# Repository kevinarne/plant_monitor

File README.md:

# Purpose
As I seek to both improve the lives of my plants and learn more about Python development, I've decided to start instrumenting my plants with some sensors like light and weight sensors.

# Current State
There are three kinds of sensors currently supported: CdS light sensor hooked up to an Arduino (directly connected to Pi via serial), CdS light sensor hooked up to an ESP32 (wireless), and load cell hooked up to an ESP32 (wireless). Each of these connects to a Raspberry Pi-hosted MySQL database on my local network.

The wireless sensors add data to the database via an HTTP request handled by a PHP script on the local server. The wired sensor is polled via serial regularly by a python script scheduled with crontab.

# Current Event Types
* 10-bit CdS light sensor (wired Arduino Nano)
* 12-bit CdS light sensor (wireless ESP32)
* Manual weighing
* Load cell weighing (wireless ESP32)
* Wiring (for shaping trees)
* Removed wire
* Root pruning
* Plant status (out of 5 stars)

# Potential Next Steps
* Visualize the collected light sensor data
* Create more ESP32-powered sensors
* Migrate from serial light sensor to ESP32 light sensor
* Add a user id column to the plant_events, sensors, and plants tables
* Convert to Flask
* Add web page to store wireless connections to ESP32 sketches
* Store tare value in EEPROM on ESP32

# Flask Conversion Next Steps
* Create routes.py
* Migrate database to an sqlite database
* Create user database
* Create web interface for adding weight
* Create plant status page
* 

# Current Tables
* plant_events - Tracks values recorded by various sensors, their associated plants, and things like watering, repotting, pruning, weighing, and even light. Currently it only tracks light.
* plants - Dictionary relating ids used in plant_events and actual plants.
* event_codes - Dictionary correlating events with unique ids.
* sensors - Details of the sensors.

# Set Up
Python 3 Libraries:
* datetime
* itertools
* python-decouple
* pyserial
* pymysql
* matplotlib
* numpy
* smtplib

See /setup/README.md for more details on setting up this project, including database setup.

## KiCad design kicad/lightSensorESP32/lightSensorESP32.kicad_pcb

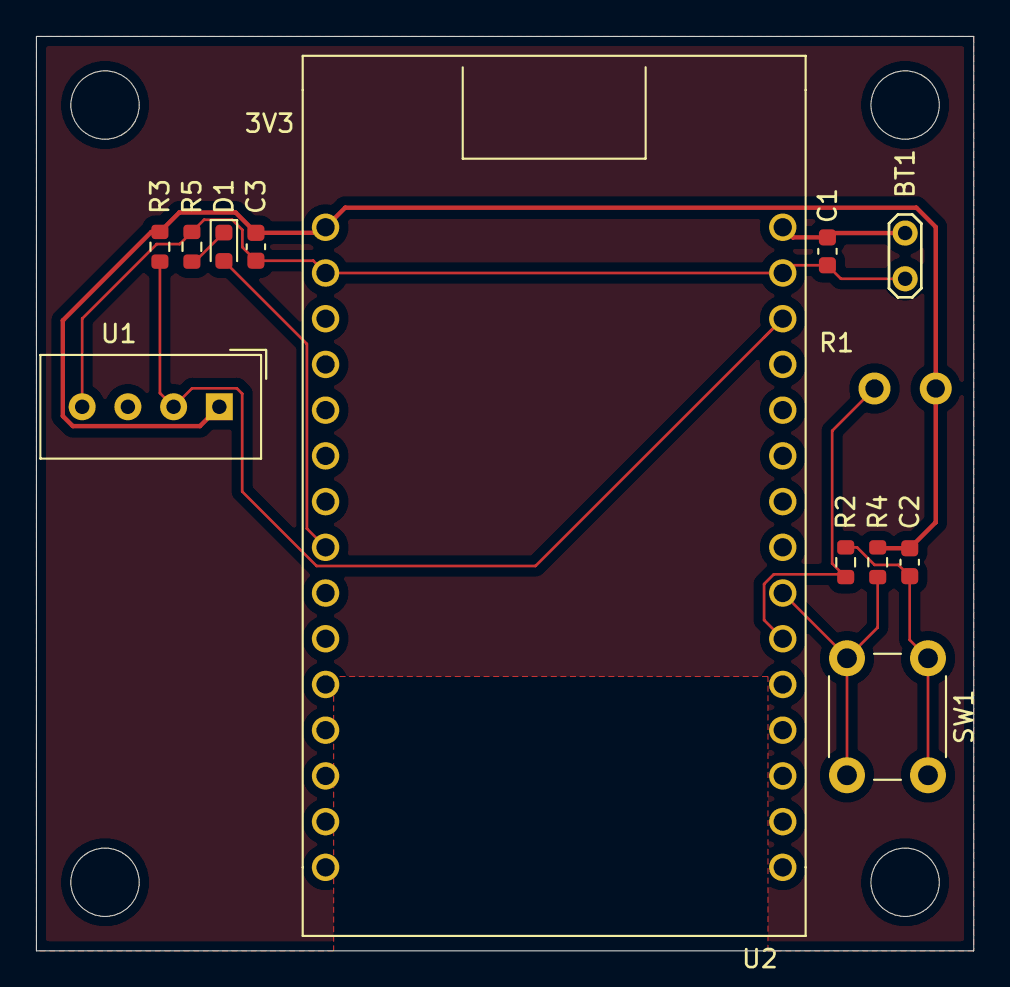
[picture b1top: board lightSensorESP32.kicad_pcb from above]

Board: 2 copper layers, 52.1 x 50.8 mm, 13 parts (0 on the bottom side), 8 nets.

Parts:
BT1: Battery_Cell; TestPoint_2Pads_Pitch2.54mm_Drill0.8mm
C1, C2, C3: CAP; C_0603_1608Metric
D1: LED; LED_0603_1608Metric
R1: R_PHOTO; CdS_Adafruit
R2, R3, R4, R5: R_Small_US; R_0603_1608Metric
SW1: SW_Push; SW_PUSH_6mm_H4.3mm
U1: DHT11; Aosong_DHT11_5.5x12.0_P2.54mm
U2: ESP32-BO

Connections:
+3V3: C2.1, C3.1, R1.1, R3.1, R4.2, U1.1, U2.1
DHT: R3.2, U1.2, U2.28
GND: BT1.2, C1.2, C2.2, C3.2, R2.2, R5.1, SW1.1, U1.4, U2.2, U2.29
LED: D1.2, U2.8
LGHT: R1.2, R2.1, U2.21
unnamed: D1.1, R5.2
SWT: R4.1, SW1.2, U2.22
VCC: BT1.1, C1.1, U2.30

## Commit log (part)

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2021-04-29 Initial commit. main.py can read raw values over USB Serial. Database has been created, but has no data in it, nor has any of the coding to put the values in the database been done.
2021-05-03 Added an integer conversion to the raw data off of the Arduino.
2021-05-03 Added menu that allows me to choose to read the sensor or exit
2021-05-04 Added empty database handler for the light value table. Updated database name in setup/README.md.
2021-05-04 Added dbtest functionality to lightdbhandler. Next is to check for the presence of a database and output an error code if not found.
2021-05-05 Added ability to log a light sensor reading to the database in main.py. Next steps are to add regular recording and clean up the code base. Input validation and credentials need to be sorted out.
2021-05-05 Added checking for credentials file to main.py. Added default menu behavior when a valid input isn't used. Removed dbtest.py.
2021-05-05 Changed main.py to take a reading every 5 minutes.
2021-05-06 Added light sensor Arduino sketch in ard folder.
2021-05-11 Database logging is now working via a cron job. Had some issues with loading the credentials as the cron job is executed from a different directory than the one I usually work from, so I had to add m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
2021-05-11 Updated README.md to reflect current state of the project.
2021-05-12 Added a utility to pull the database and turn it into a csv to be easily read by Excel or Google Sheets.
2021-05-16 Not sure what I did but I'm logging where I started today.
2021-05-17 Worked a little more on the sqlmanager. Next step is to make it possible to create generic tables using a list of column attributes.
2021-05-17 Got the mysqlmanager to read in the credentials. Next step is implementing the database creation aspects.
2021-05-17 Database creation with sqlmanager appears to be working.
2021-05-18 Slowly adding to the table creation function.
2021-05-18 Updated README.md to reflect current state and next steps.
2021-05-20 Added some error handling to the database connections using sqlmanager.py. Clarified when the database is created and specified.
2021-05-23 Implemented add_values function to add values to a specified table. Needs a way to validate that the proper values have been provided for a given table as well as error handling when things aren't ad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
2021-05-23 Tested and improved a general purpose add value function to add values to any table. Needs some error handling.
2021-05-24 Now able to add plants to the plants table.
2021-05-25 Cosmetic changes to sqlmanager.py to make the table creation slightly more readable.
2021-05-25 Renamed main.py to read_light.py to transition to calling a centralized sensor polling script and reserve main for user-facing activities like visualizing data or adding new plants.
2021-05-25 Updated read_light.py to eliminate the need for lightdbhandler.py. Need to add com port scanning instead of hard coding the com port.
2021-05-25 Set read_light.py to accept some parameters so it could be properly called from both the command line and the crontab, since those require different relative paths to the credentials file. Will need 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
2021-05-25 Tweaked names some more as a read_light.py somehow got duplicated, should be correct now.
2021-05-26 Updated some of the setup README.md.
2021-05-27 Added .gitignore file.
2021-05-27 Not exactly sure what I changed last night, but bookmarking today's start with a commit.
2021-05-28 Added a menu option for adding sensors (though it isn't connected to anything yet) in main. Eliminated some print statements from sqlmanager.py.
2021-05-28 Changed name of addplants to addentries to start using it for adding entries to all of the tables. I've debated rolling this into the sqlmanager.py script, but decided against it so far.
2021-05-31 Started the creation of a script to migrate the light values from the old light table to the new plant_event table to more effectively capture the data coming off of a variety of sensors.
2021-05-31 Script for migrating to the event table is ready once one line is uncommented. Next up is re-directing the sensor polling to save the data in the plant_events table.
2021-06-03 Set the migratetoevent script to actually write to the plant_event database. The light readings are now being logged in the plant_event table. The light_val table is now deprecated.
2021-06-04 Updated README file to reflect recent updates.
2021-06-05 Successfully setup the connection between the database and the script to add event codes.
2021-06-05 Updated README.md to reflect current status.
2021-06-05 Implemented date input for adding events.
2021-06-07 Moved menu actions in main.py to functions to make the main loop more readable. Added a menu option to read all of the values from a table of the user's choice.
2021-06-07 Added input statements to pull get information about events.
2021-06-08 Added event code checking when adding an event manually. Next up is actually adding the data to the database.
2021-06-08 Added an event adding function to the addentries script. Finished implementation of event adding to main.py
2021-06-08 Added script to take a csv of my current plant weights and add it to the plant_events table.
2021-06-09 Changegd sqlmanager.py to pull the credentials from environmental variables instead of a credentials file. Still need to remove the credential path variable from the MySqlManager constructor as well 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
2021-06-09 I think I got everywhere that the old MySqlManager constructor was called.
2021-06-09 Corrected the script to manually add weights from a csv file.
2021-06-10 Created backup script to pull the entire database and store it in separate .csv files.
2021-06-10 Added some new next steps to the README.md
2021-06-11 Implemented last day watered algorithm.
2021-06-12 Added a default option of using today's date when adding an event.
2021-06-12 Tweaked the plant status to give the last date of watering and the last weight at watering. Added a plant event class to make the plant status logic easier to read.
2021-06-12 Updated README.md.
2021-06-14 Cleaned up sqlmanager.py to make it more general purpose. I would like to create a setup script that handles the table creation.
2021-06-15 Added display of plants to the plant status prompt.
2021-06-15 edited setup script (still needs lots of work). Updated README.md file to represent next steps.
2021-06-15 Added some basic php to connect to the MySql database.
2021-06-16 Added a wireframe display page.
2021-06-16 Removed echos from the mysqli_connect.php.
2021-06-17 Testing addweight layout for web interface.
2021-06-17 addweight.php displays proper plant options now. Created a file for handling actually putting the data in the database.
2021-06-18 Weights can now be added through the web portal. Still need to have the page redirect back to the add weight page and signal a successful addition.
2021-06-18 Fixed bug resulting from different date string formats in python and php by truncating the datetime string after the seconds place. Nothing changes that fast on plants.
2021-06-20 Edited spacing in main.py and sqlmanager.py to better conform to Google style guidelines. Added a few more files to .gitignore.
2021-06-22 Added some VERY rudimentary styling to the addweight.php page to make it easier to use on my phone.
2021-06-24 Set up an ESP32 to send basic HTTP requests that interface with the newly-created remotelight.php. Next up is fleshing out the php script to add data from the ESP32 to the database.
2021-06-24 Added ESP32 wifi credentials file to .gitignore.
2021-06-24 Added some debugging output to remotelight.php.
2021-06-24 Implemented plant status in php so I can now access the plant statuses from my phone easily. This page details when each plant was last watered, at what weight, and what the current weight is.
2021-06-26 Fleshed out php page for adding a light sensor's readings to the database. Currently iterates through the appropriate plants and adds dummy data. Needs to be changed to add real data.
2021-06-28 Remoted csvtoevent.py as it was no longer needed.
2021-06-28 Removed test display php page.
2021-06-28 Previous commit omitted the line in the main loop that actually polled the sensor. This has been fixed.
2021-06-29 Updated README.md to reflect some new next steps.
2021-06-29 Fixed remotelight.php and tested with a quick python script.
2021-06-29 Changed remotelight.php to use GET instead of POST for ease of coding on the ESP32.
2021-07-01 Updated next steps in README.md. Improved Arduino script to read light sensor.
2021-07-01 Updated light sensor script to allow for configurable sensor and event ids.
2021-07-02 Marginally improved the plant status graphs by removing the dates.
2021-07-03 Added sensor template Arduino script based on the light sensor script.
2021-07-03 Added wireframe of weight sensor.
2021-07-03 Updated the weight Arduino script to use the remotelight.php script for inputting values.
2021-07-03 Updated remotelight.php to encode the source string too.
2021-07-05 Added a return to the execute_mysql. Created a check sensors scripts to export the most recent entry under each sensor.
2021-07-05 Made some minor tweaks to the sensor checker script. Currently the serial light sensor isn't being added to the database correctly. Need to design a PCB to make it easier to wire up new light sensors.
2021-07-07 Started schematic for a board to simplify wiring light sensors. May choose to include humidity and temperature sensors too to round out a weather sensor station.
2021-07-10 Started script to visualize differences between the weight sensor and manually recorded weight.
2021-07-10 Running into some incompatibilities between the ways datetimes are being encoded by the manual records and weight sensor. I can tweak the existing data to work with the current script, but I should a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
2021-07-12 Updated remotelight.php to change the datetime string encoding issue. Will need to clean up the database too.
2021-07-16 Added DHT11 and ESP32 to light sensor schematic.
2021-07-18 Added comments to sqlmanager. Tweaked weight visualization script.
2021-07-19 Removed plantevents file as it was unused.
2021-07-20 Added a cleaning script for the datetime issues. Will likely delete in the next commit.
2021-07-21 Updated check sensors script to send emails when it has been more than a day since the sensor checked in.
2021-07-21 Updated some next steps in README.md
2021-07-22 Really struggling with the weight Arduino script. Core problem is loading the network credentials from Preferences and converting them to the right form for the WiFi library.
2021-07-22 Removed Arduino scripts from this repository. They will be moved to a different repo that I'll post shortly.
2021-07-23 Removed readlight.py because I'm switching to entirely IoT-based sensors rather than wired ones.
2021-07-23 Moved the plant adding features to a separate addplant utility.
2021-07-24 Moved event code adding to util/addeventcode.py
2021-07-24 Moved event adding to its own addevent.py file.
2021-07-24 Marging simplyifymain (ugh, misspelled) into main.
2021-07-28 Added LED and switch to light sensor schematic. Next up is laying out the board.
2021-08-17 Added some extra comments to checksensors.py to clarify how it works.
2021-08-19 Added a way to toggle sensors between active and inactive.
2021-08-26 Changed pathing for backups. Fixed inconsistent datetime string during csv output.
2021-09-08 Fixed export table issue in main.py
2022-01-17 Fleshed out models.py. Needs another glance to be sure everything is properly translated.
2022-01-23 Updated some of the next steps and added more granularity to the Flask conversion steps.
